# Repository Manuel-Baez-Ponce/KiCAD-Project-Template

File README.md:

View this project on [CADLAB.io](https://cadlab.io/project/29603).

<h1 align=center style='color: #26368E;'>KiCAD Project Templates</h1>

This is my personal project templates collection for KiCAD, it includes the definition and specifications for a variety of boards and projects.

Each project template is composed as the next diagram:

Project template directory/  
├── meta/  
│ ├── A image of 64x64 pixels named icon.(jpg or png)  
│ ├── The info.html archive with a resume of the project  
│ └── Others complementary files and images  
├── *.Kicad_pcb  
├── *.kicad_pro  
└── *.kicad_sch

Also the main directory is composed of the next templates:

template/  
├── CH32v307EVTR1/  
├── EPM240Blue/  
├── EPM240Red/  
├── ESP32DevKit/  
├── PmodV1/  
└── PmodV2/

## How to use the project

1. In a terminal go to the Kicad template directory, normaly in the next location ~/documents/kicad/\*/
2. Clone the project in a temporal directory.
3. Copy the content in the template directory.

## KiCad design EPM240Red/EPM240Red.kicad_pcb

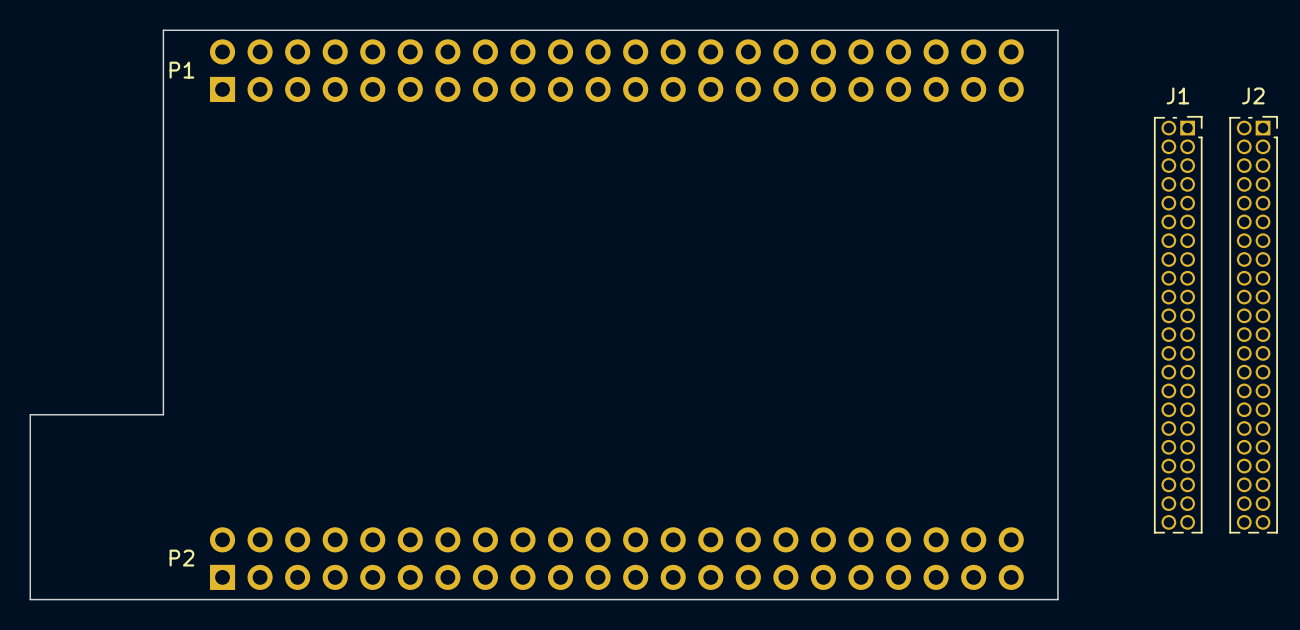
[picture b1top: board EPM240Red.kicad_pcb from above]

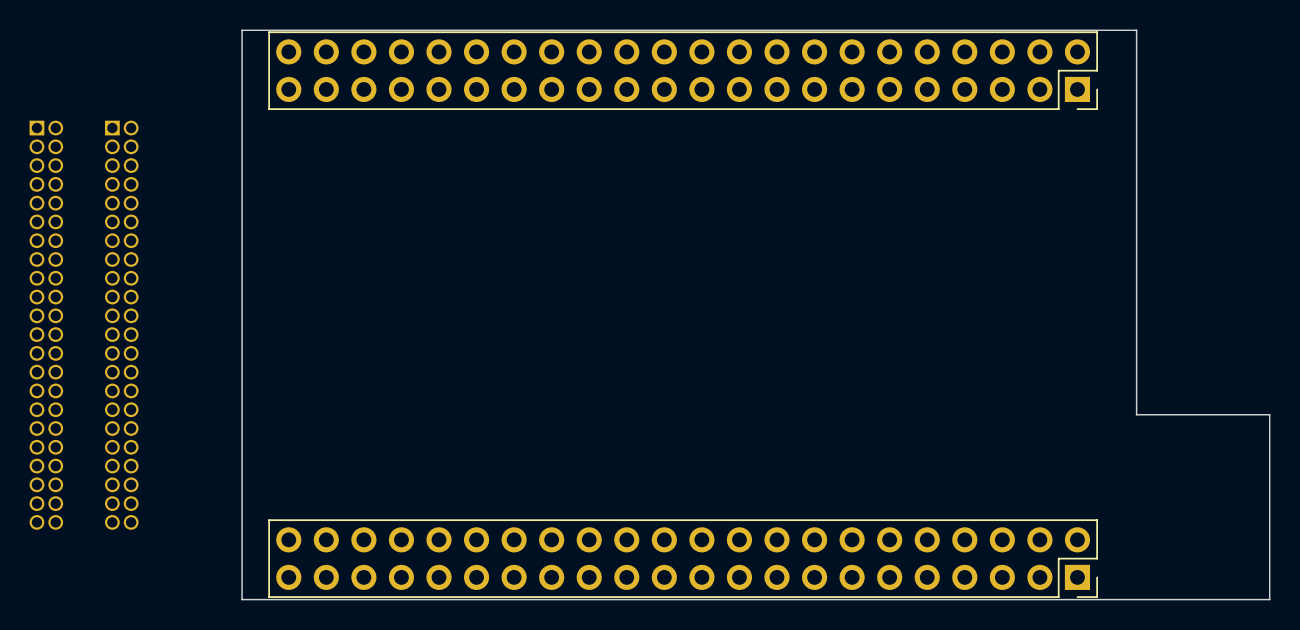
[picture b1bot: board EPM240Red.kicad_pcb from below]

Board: 2 copper layers, 69.5 x 38.5 mm, 4 parts (2 on the bottom side), 2 nets, no tracks yet.

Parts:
J1, J2: Conn_2x22; PinSocket_2x22_P1.27mm_Vertical
P1, P2: Conn02x21; PinSocket_2x22_P2.54mm_Vertical

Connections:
GND: J1.2, J1.43, J1.44, J2.2, J2.43, J2.44, P1.1, P1.41, P1.42, P2.1, P2.41, P2.42
VCC: J1.1, J2.1, P1.2, P2.2

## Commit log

2025-09-22 Add README.md and .gitignore
2025-09-22 Add currently projects templates
2025-09-22 Modified README file
2025-09-22 Backlink to CADLAB.io has been added.
2025-09-22 Make a correction in the diagrams of README file
2025-09-22 Delate the 'p' Tags in the CADLab.io link in README file
2025-09-23 Define the Edge and minimal footprints positions in CH32V307 template.
2025-09-24 Modified CH32V307EVTR1 info file to include an example image and code resources
2025-09-24 Modified the Titles in info files
2025-09-24 Add Example images
2025-09-24 Add ESP32DevKit kicad files
2025-09-26 Add ESP32DevKit info file and auxiliar images
2025-09-26 Define a name for the EPM240 expansion boards
